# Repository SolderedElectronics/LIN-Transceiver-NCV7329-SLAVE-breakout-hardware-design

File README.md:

# <INSERT PRODUCT NAME> Hardware Design

## About the Product

|  |
| :----------------------------------------------------------: |
| [Buy <INSERT PRODUCT NAME>](https://www.solde.red/333027) |

LIN (Local Interconnect Network) is a serial network protocol used for communication between components in cars. The LIN bus is an alternative to the CAN bus, and the difference is that LIN has a lower speed and supports a smaller number of simultaneous devices, but also has drastically lower costs. LIN is used for communication between microcontrollers. The operating voltage is 18V.

Master/Slave is a communication model where one device (Master) controls one or more devices (Slave), and the Slave then listens to the commands it receives from the Master. One Master on the LIN protocol can control up to 16 devices.

---

## Repository Contents

This repository contains all design files for <INSERT PRODUCT NAME>, organized as follows:

- **`CAD` folder**: Contains KiCAD design files, including:
  - Schematics
  - PCB layout
  - Panel PCB layout
  - Source 3D files in Fusion360, if any
  - All files are sorted by version with a detailed change log.
- **`OUTPUTS` folder**: Includes all production-ready files, such as:
  - Bill of Materials (BOM) and interactive BOM (iBOM)
  - PDF versions of schematics
  - 3D `.step` file of the board
  - 3D-printable models
  - Gerber files for PCB manufacturing
  - Image of the pinout of the board
  - Product image
  - Compliance, legal and generic sales documents

Refer to the `Change Log` in the CAD folder for details about updates between versions.

---

## Learn More About the Product

Beyond the repository, explore the following resources:

### Soldered Verify

The **Soldered Verify** system ensures every board you purchase from Soldered is fully functional. It also provides access to exclusive test data for your product. To get started, find the unique Soldered Verify ID on your product's packaging and enter the ID on the [Soldered Verify page](https://soldered.com/verify/) to access test results and additional product details.

### Soldered Community

Soldered Community is your go-to place for technical support. Our engineers track and answer all questions posted there, and it’s a great space for the maker community. Get answers to your questions and solutions for your challenges at [Soldered Community](https://soldered.com/community).

### solde.red

solde.red is an ultimate URL shortener and information hub. Access it by typing solde.red/ followed by your product SKU, e.g., [solde.red/333000](https://solde.red/333000), to find getting-started guides, datasheets, open-source hardware and software files, certifications, images, pinouts, and more. Read more about the shortener [here](https://solde.red/info/).

---

## Contributing

Contributions are welcome! Here’s how you can get involved:

- Submit pull requests to enhance the design or fix issues.
- Report bugs or problems by opening an issue.

We encourage community collaboration to make this product even better.

---

## About Soldered

[Soldered for Makers](https://soldered.com) specializes in designing and manufacturing electronic products tailored for enthusiasts, ranging from hobbyists to professionals. Our portfolio includes electronic boards, sensors, and actuators that are widely utilized in fields such as microelectronics, mechatronics, robotics, programming, and IoT. Every product we offer is designed in-house and built upon open-source hardware and software platforms. Proudly certified and manufactured within the European Union, our catalog likely includes the product you need for your project.

We complement these products with comprehensive tutorials and manuals, product descriptions, schematics, programming codes, and project examples. Our round-the-clock [customer and technical support](https://soldered.com/community) is available for all our products, irrespective of the sales channel. Soldered’s success and services reflect our maker community’s unwavering [trust](https://www.trustpilot.com/review/soldered.com), for which we are deeply grateful. Join our community and create using Soldered products.

---

## License

All Soldered open-source hardware (OSH) is under The TAPR Open Hardware License. Read more in the LICENSE file located in this repository.

**Disclaimer:**

No warranty - all designs in this repository are distributed in the hope that they will be useful, but without any warranty. They are provided "AS IS", therefore without warranty of any kind, either expressed or implied. The entire quality and performance of what you do with the contents of this repository are your responsibility. In no event Soldered Electronics will be liable for your damages, or losses, including any general, special, incidental, or consequential damage arising out of the use or inability to use the contents of this repository. 

---

## Have fun!

Thank you for your support from your fellow makers at Soldered Electronics.

Happy Making!

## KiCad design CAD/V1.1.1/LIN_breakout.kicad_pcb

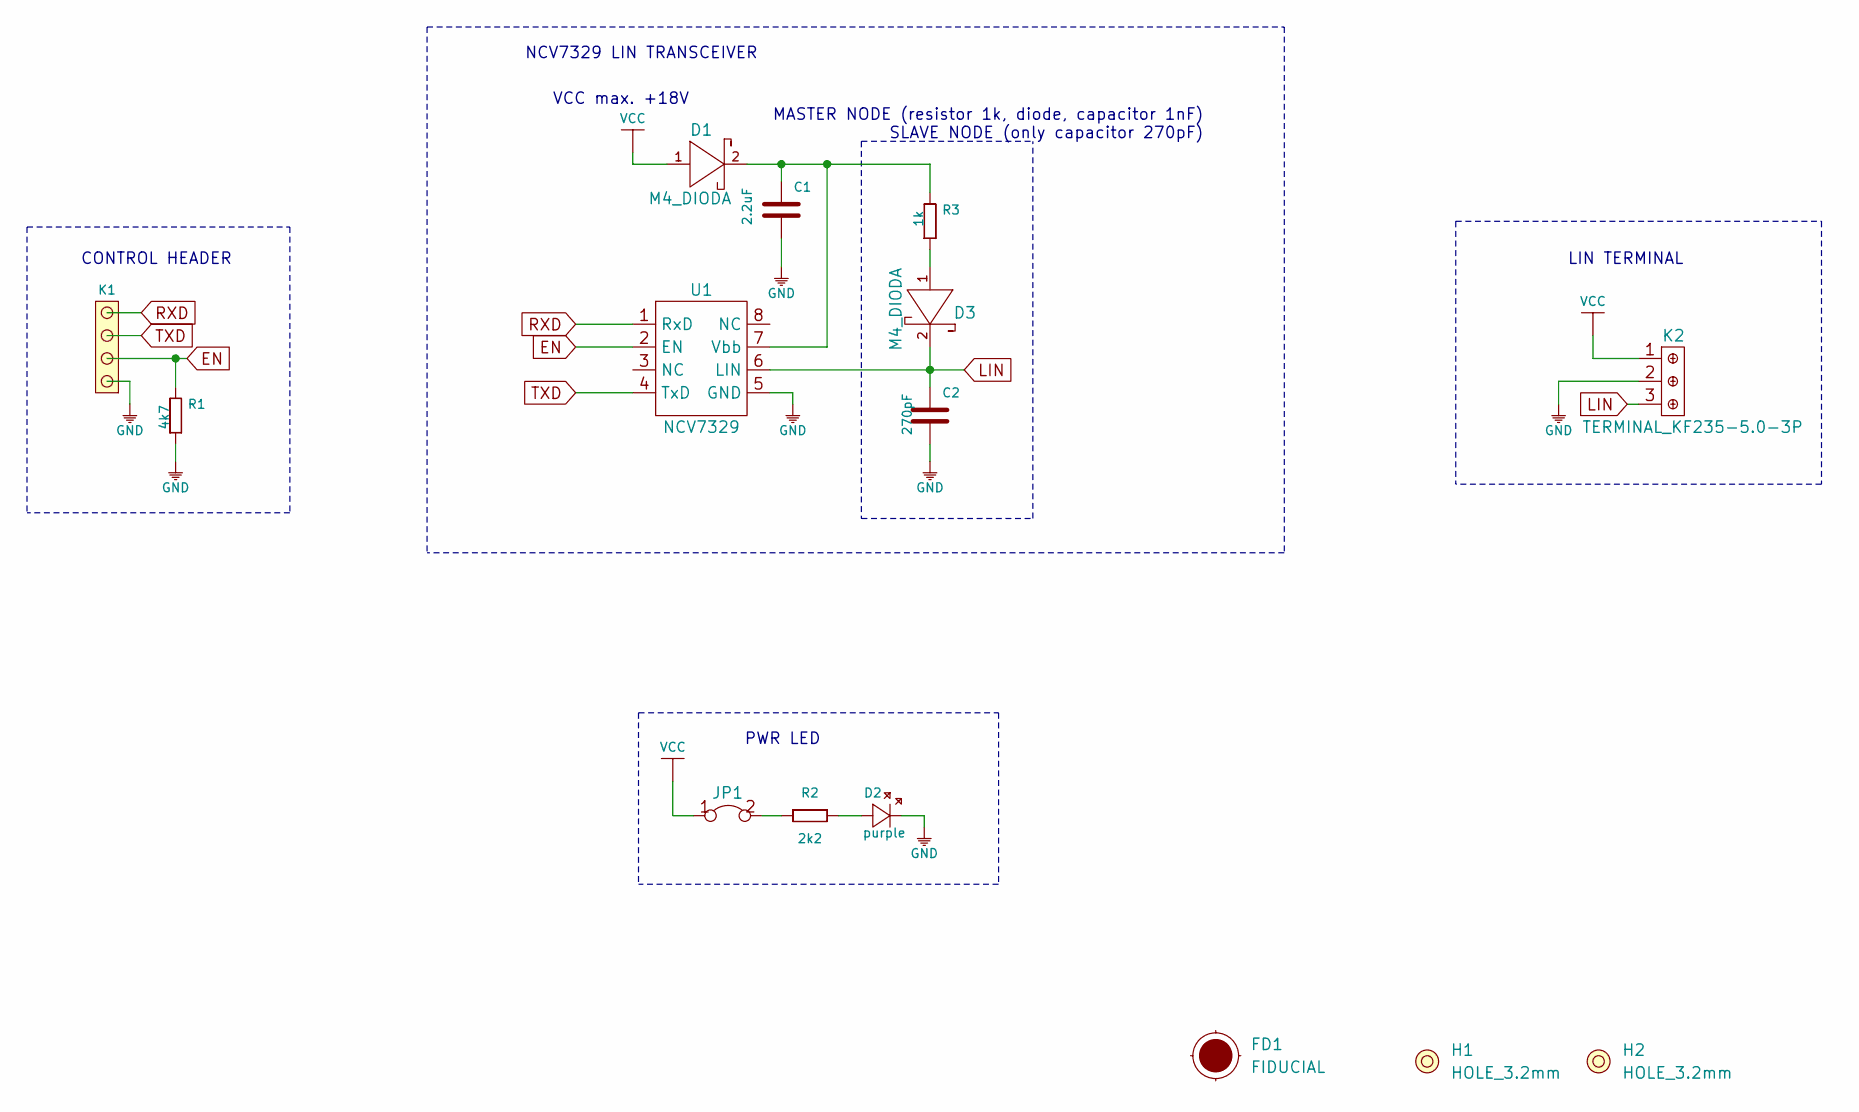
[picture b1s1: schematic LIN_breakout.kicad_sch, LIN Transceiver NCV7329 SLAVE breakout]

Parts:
C1: 2.2uF; 0603C
C2: 270pF; 0603C
D1, D3: M4_DIODA
D2: purple; 0402LED
FD1: FIDUCIAL; FIDUCIAL_23
H1, H2: HOLE_3.2mm
JP1: SMD-JUMPER-CONNECTED_TRACE_SLODERMASK
K1: HEADER_MALE_4X1
K2: TERMINAL_KF235-5.0-3P
R1: 4k7; 0603R
R2: 2k2; 0402R
R3: 1k; 0603R
U1: NCV7329; SOIC−8

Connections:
EN: K1.2, R1.2, U1.2 (EN)
GND: C1.1, C2.1, D2.2 (K), K1.1, K2.2, R1.1, U1.5 (GND)
LIN: C2.2, D3.2 (K), K2.3, U1.6 (LIN)
unnamed: C1.2, D1.2 (K), R3.2, U1.7 (Vbb)
unnamed: D2.1 (A), R2.2
unnamed: D3.1 (A), R3.1
unnamed: JP1.2, R2.1
RXD: K1.4, U1.1 (RxD)
TXD: K1.3, U1.4 (TxD)
VCC: D1.1 (A), JP1.1, K2.1

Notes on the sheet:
NCV7329 LIN TRANSCEIVER
VCC max. +18V
LIN TERMINAL
CONTROL HEADER
MASTER NODE (resistor 1k, diode, capacitor 1nF) SLAVE NODE (only capacitor 270pF)
PWR LED

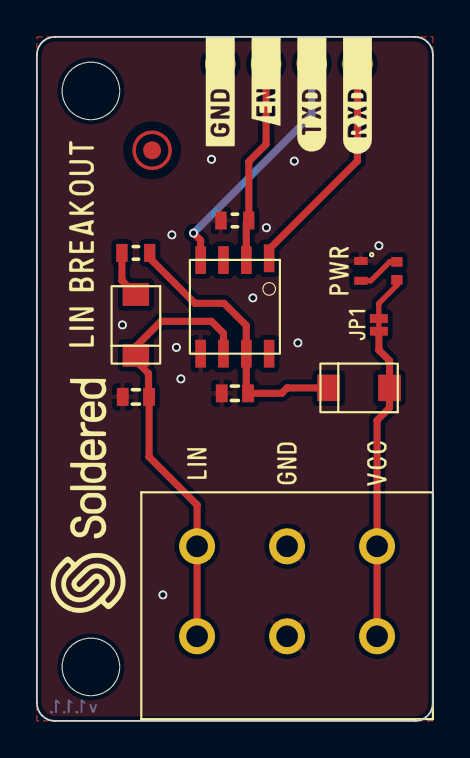
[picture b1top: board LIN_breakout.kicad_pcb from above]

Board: 2 copper layers, 22.0 x 38.0 mm, 15 parts (1 on the bottom side), 10 nets.

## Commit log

2022-08-06 Updating open source files.
